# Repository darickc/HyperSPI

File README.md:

# HyperSPI
SPI bridge for AWA protocol to control a LED strip from HyperHDR.  
Diagnostic and performance data available at the serial port output [read more](#performancedebug-output).  
Raspberry Pi acts as a master, ESP8266/ESP32/ESP32-S2/rp2040(Raspberry Pi Pico) is in slave mode. 
  
| LED strip / Device             | rp2040 / Pico | ESP8266<br>(limited performance) |    ESP32 / ESP32-S2 mini    
|--------------------------------|:-------:|:-----------:|:-------:|
| SK6812 cold white              |   yes   |   yes   |     yes     |
| SK6812 neutral white           |   yes   |   yes   |     yes     |
| WS281x                         |   yes   |   yes   |     yes     |

# Why this project was created?

- SPI is very faster. HyperSPI works best at speed over 20Mb
- SPI doesn't have any data integration check. But AWA protocol does have one
- you don't need to have 2Mb capable serial port on your ESP board
- SPI transmission is much lighter than serial communication
- There is a hardware limitation for the Rpi current design...even if you connect your grabber using USB2.0 mode, working serial port driver (used by Adalight) results in quite a large drop in overall USB transfer. So we can replace Adalight with a pure SPI data transfer as an alternative
- I needed it and I was able to implemented it 😉

# Hardware connection  

If you are using an ESP board compatible with the Wemos board (ESP8266 Wemos D1/pro, ESP32 MH-ET Live, ESP32-S2 lolin mini), the SPI connection uses the same pinout location on the ESP board! The pin positions of the LED output may vary. Cables (including ground) should not exceed 15-20cm or it may be necessary to lower the SPI speed. 

The photos below use the same home-made adapter throughout, so you can see a repeating pattern and the cable colors should help you locate the correct pins. However, always consult the GPIO diagram for your boards to confirm that you have connected the cables correctly, because if you make a mistake and connect to the 5V GPIO line, it may damage both devices.  

As you can also notice, the pinout of the SPI0 interface is identical for the entire Raspberry Pi SBC family: 3, 4, 5, Zero 2W, etc.  

<table>  
  <tr>
    <td colspan="2"><p align="center">See how easy it is to connect Raspberry Pi Pico (rp2040) to Raspberry Pi 5 using SPI</p></td>    
  </tr>
  <tr>
    <td colspan="2"></td>
  </tr>
  <tr>
    <td></td>
    <td></td>
  </tr>
  <tr>
    <td colspan="2"><p align="center">or if you prefer ESP32/ESP32-S2/Esp8266</p></td>
  </tr>
  <tr>
    <td></td>
    <td></td>
  </tr>
  <tr>
    <td></td>
    <td></td>
  </tr> 
  <tr>
    <td colspan="2"><p align="center">multi-architecture support via FTDI (ex. FT232H)</p></td>
  </tr>
  <tr>
    <td colspan="2"></td>    
  </tr>  
</table>

# Example of supported boards

<p align="center">
<b>Adafruit RP2040 Scorpio and ItsyBitsy with built-in level shifter (recommended!)</b><br/>  

</p>

<p align="center">
<b>Esp8266 Wemos D1 mini (CH340) and Wemos D1 mini pro (CP2104)</b><br/>

</p>

<p align="center">
<b>ESP32 MH-ET Live and ESP32-S2 Lolin mini (CDC)</b><br/>

</p>

## Default pinout (can be changed for esp32, esp32-s2 and rp2040 Pico)
  
|    PINOUT   |  ESP8266  |   ESP32   | ESP32-S2 | Pico (rp2040) | Adafruit rp2040<br/>Scorpio / ItsyBitsy
|-------------|-----------|-----------|-----------|-----------|-----------|
| Clock (SCK) | GPIO 14   | GPIO 18   | GPIO 7    | GPIO 2    | GPIO 26 (A0) |
| Data (MOSI) | GPIO 13   | GPIO 23   | GPIO 11   | GPIO 4    | GPIO 28 (A2) |
| SPI Chip Select(e.g. CE0) | not used    | GPIO 5    | GPIO 12   | GPIO 5    | GPIO 29 (A3) |
| GROUND      | mandatory | mandatory | mandatory | mandatory | mandatory |
| LED output  | GPIO 2    | GPIO 2    | GPIO 2    | GPIO 14 | GPIO16 / GPIO14 |

> [!CAUTION]
> The ground connection between both GPIOs is as important as the other SPI data connections. The ground cable should be of a similar length as them and run directly next to them.

# Flashing the firmware

There are two versions of the firmware for ESP32 and ESP32-S2. The 'factory' (in the `recovery_firmware.zip` archive) and the 'base' one. Factory firmware should be flashed to offset 0x0, base firmware to offset 0x10000.

## Flashing ESP32-S2 Lolin mini

Requires using `esptool.py` to flash the firmware e.g.  
 - `esptool.py write_flash 0x10000 hyperspi_esp32_s2_mini_SK6812_RGBW_COLD.bin` or
 - `esptool.py write_flash 0x0 hyperspi_esp32_s2_mini_SK6812_RGBW_COLD.factory.bin`

Troubleshooting: ESP32-S2 Lolin mini recovery procedure if the board is not detected or is malfunctioning.  
1. Put the board into dfu mode using board buttons: press `Rst` + `0` buttons, then release `Rst`, next release `0`  
Do not reset or disconnect the board until the end of the recovery procedure.
2. Execute `esptool.py erase_flash`  
3. Flash 'factory' version of the firmware e.g.  
`esptool.py write_flash 0x0 hyperspi_esp32_s2_mini_SK6812_RGBW_COLD.factory.bin`  
4. **`esptool.py` is not able to automatically reset esp32-s2 when in dfu mode. Reconnect or hard reset it manually.** The board should be detected as a COM port in the system.

## Flashing generic Esp8266/ESP32

Recommend to use [esphome-flasher](https://github.com/esphome/esphome-flasher/releases)  
Or use `esptool.py` e.g.  
 - `esptool.py write_flash 0x10000 hyperspi_esp32_SK6812_RGBW_COLD.bin` or
 - `esptool.py write_flash 0x0 hyperspi_esp32_SK6812_RGBW_COLD.factory.bin`

For **RGBW LED strip** like RGBW SK6812 NEUTRAL white choose: *hyperspi_..._SK6812_RGBW_NEUTRAL.bin*  
For **RGBW LED strip** like RGBW SK6812 COLD white choose: *hyperspi_..._SK6812_RGBW_COLD.bin*  
For **RGB LED strip** like WS8212b or RGB SK6812 variant choose: *hyperspi_..._WS281x_RGB.bin*  

## Flashing Pico boards

It's very easy and you don't need any special flasher.  

Use firmware from the `hyperspi_pico_rp2040.zip` archive. Adafruit boards have their own custom firmware package inside the archive: `Adafruit_ItsyBitsy_RP2040.zip` and `Adafruit_Feather_RP2040_Scorpio.zip`

Put your Pico board into DFU mode:  
* If your Pico board has only one button (`boot`) then press & hold it and connect the board to the USB port. Then you can release the button.
* If your Pico board has two buttons, connect it to the USB port. Then press & hold `boot` and `reset` buttons, then release `reset` and next release `boot` button.  

In the system file explorer you should find new drive (e.g. called `RPI-RP2` drive) exposed by the Pico board. Drag & drop (or copy) the selected firmware to this drive. 
The Pico will reset automaticly after the upload and after few seconds it will be ready to use.
  
# Software configuration (HyperHDR v17 and above)

**In HyperHDR `Image Processing→Smoothing→Update frequency` you should do not exceed the maximum capacity of the device. Read more here: [testing performance](https://github.com/awawa-dev/HyperSPI#performance-output)**

Select `esp8266` protocol for ESP proprietary SPI protocol, `esp32` for ESP32 boards, `rp2040 (Pico)` for Pico boards or `standard` for other devices.    
Make sure you set "Refresh time" to zero, "Baudrate" should be set to high but realistic value like ```25 000 000```.  
Enabling "White channel calibration" is optional, if you want to fine tune the white channel balance of your sk6812 RGBW LED strip.

# Benchmark results

## ESP32 & ESP32-S2 parallel multi-segment mode

| sk6812 LED strip / Device                                                                      | ESP32 MH-ET LIVE mini<br/>HyperSPI v9 |  ESP32-S2 Lolin mini<br/>HyperSPI v9 |
|-----------------------------------------------------------------------------------------|-----------------------|----------------------|
| 300 RGBW LEDs<br>Refresh rate/continues output=100Hz<br>SECOND_SEGMENT_START_INDEX=150 |          100          |          100         |
| 600 RGBW LEDs<br>Refresh rate/continues output=83Hz<br>SECOND_SEGMENT_START_INDEX=300  |           83          |           83         |
| 900 RGBW LEDs<br>Refresh rate/continues output=55Hz <br>SECOND_SEGMENT_START_INDEX=450 |         54-55         |           55         |

## SP8266 / ESP32

| sk6812 LED strip / Device                             | ESP32 MH ET Live<br/>HyperSPI v9 | ESP32-S2 Lolin mini<br/>HyperSPI v9 | ESP8266 Wemos D1 Pro<br/>HyperSPI v9 |
|------------------------------------------------|-----------------|--------------------|---------------------|
| 300 RGBW LEDs<br>continues output=83/70Hz  |        83       |          83        |          70         |
| 600 RGBW LEDs<br>continues output=43/33Hz  |      42-43      |          42        |          33         |
| 900 RGBW LEDs<br>continues output=28/22Hz  |       28        |          28        |          22         |

# Compiling

## ESP8266 / ESP32

Currently we use PlatformIO to compile the project. Install [Visual Studio Code](https://code.visualstudio.com/) and add [PlatformIO plugin](https://platformio.org/).
This environment will take care of everything and compile the firmware for you. Low-level LED strip support is provided by my highly optimizated (pre-fill I2S DMA modes, turbo I2S parallel mode for up to 2 segments etc) version of Neopixelbus library: [link](https://github.com/awawa-dev/NeoPixelBus).

## Pico rp2040

Use Pico SDK and Visual Code to open ```rp2040``` folder. Edit ```rp2040\CMakeLists.txt``` configuration file if you need to apply changes.

## Github Action

But there is also an alternative and an easier way. Just fork the project and enable its Github Action. Use the online editor to make changes:
- esp8266/ESP32 boards: to the ```platformio.ini``` file
- rp2040 Pico boards: to the ```rp2040\CMakeLists.txt``` file

for example change default pin-outs or enable multi-segments support, and save it. Github Action will compile new firmware automatically in the Artifacts archive. It has never been so easy! **Just remember to follow the steps in the correct order otherwise the Github Action may not be triggered the first time after saving the changes.**

Tutorial: https://github.com/awawa-dev/HyperSPI/wiki

# Multi-Segment Wiring (ESP32, ESP32-S2 and Pico rp2040 boards only)

## ESP32

Using parallel multi-segment allows you to double your Neopixel (e.g. sk6812 RGBW) LED strip refresh rate by dividing it into two smaller equal parts. Both smaller segments are perfectly in sync so you don't need to worry about it. Proposed example of building a multisegment:
- Divide a long or dense strip of LEDs into 2 smaller equal parts. So `SECOND_SEGMENT_START_INDEX` in the HyperSPI firmware is the total number of LEDs divided by 2.
- Build your first segment traditional way e.g. clockwise, so it starts somewhere in middle of the bottom of frame/TV and ends in the middle of the top of frame/TV
- Start the second segment in the opposite direction to the first one e.g. counterclockwise (`SECOND_SEGMENT_REVERSED` option in the HyperSPI firmware configuration must be enabled). So it starts somewhere in the middle of the bottom of the frame/TV and ends in the middle of the top of the TV/frame. Both segments could be connected if possible at the top but only 5v and ground ( NOT the data line).
- The data line starts for both segments somewhere in the middle of the bottom of the TV/frame (where each of the LED strips starts)
- Configuration in HyperHDR does not change! It's should be configured as one, single continues segment. All is done in HyperSPI firmware transparently and does not affect LED strip configuration in HyperHDR.

You also must configure data pin in the `platformio.ini`. Review the comments at the top of the file:
* `SECOND_SEGMENT_DATA_PIN` - These is data pin for your second strip

You add these to your board's config. Be sure to put `-D` in front of each setting. 

Examples of final build_flags for 288 LEDs divided into 2 equal segments in the `platformio.ini`:
```
[env:SK6812_RGBW_COLD]
build_flags = -DNEOPIXEL_RGBW -DCOLD_WHITE -DDATA_PIN=2 ${env.build_flags} -DSECOND_SEGMENT_START_INDEX=144 -DSECOND_SEGMENT_DATA_PIN=4 -DSECOND_SEGMENT_REVERSED
...
[env:WS281x_RGB]
build_flags = -DNEOPIXEL_RGB -DDATA_PIN=2 ${env.build_flags} -DSECOND_SEGMENT_START_INDEX=144 -DSECOND_SEGMENT_DATA_PIN=4 -DSECOND_SEGMENT_REVERSED
...
```
Implementation example:
- The diagram of the board for WS2812b/SK6812 including ESP32 and the SN74AHCT125N 74AHCT125 [level shifter](https://github.com/awawa-dev/HyperHDR/wiki/Level-Shifter).

## Pico rp2040

Edit ```rp2040\CMakeLists.txt``` file and recompile the project.

# Automatic LED Power Control (ESP32)

HyperSPI can optionally drive a relay (or a MOSFET power switch) that disconnects the **positive 5V supply of the LED strip** when there is nothing to display, similar to the relay feature of WLED and HyperSerialESP32. The feature is compiled in only when `LED_POWER_PIN` is defined. Without it the firmware behaves exactly as before.

Tested target: ESP32-WROOM-32 (`esp32dev`). The code only uses `pinMode`/`digitalWrite`/`millis`, but other boards have not been verified.

## How to enable it

Use one of the ready-made environments. Both use data on GPIO2 and an active-high power switch on GPIO16, matching the P-MOSFET board in [`hardware/hyperspi-led-controller`](hardware/hyperspi-led-controller):

| LED strip | Environment | Firmware |
|---|---|---|
| SK6812 RGBW cold white | `SK6812_RGBW_COLD_LED_POWER` | `hyperspi_esp32_SK6812_RGBW_COLD_LED_POWER.bin` |
| WS281x RGB (WS2812B etc.) | `WS281x_RGB_LED_POWER` | `hyperspi_esp32_WS281x_RGB_LED_POWER.bin` |

```
pio run -e SK6812_RGBW_COLD_LED_POWER
```
You can also append the flags to the `build_flags` of any ESP32 environment in `platformio.ini`:
```ini
; active-low relay module (IN = LOW switches the LED power on)
build_flags = -DNEOPIXEL_RGB -DDATA_PIN=2 ${env.build_flags} -DLED_POWER_PIN=16 -DLED_POWER_INVERT

; active-high relay module or MOSFET board (IN = HIGH switches the LED power on)
build_flags = -DNEOPIXEL_RGB -DDATA_PIN=2 ${env.build_flags} -DLED_POWER_PIN=16
```

| Flag | Default | Description |
|---|---|---|
| `LED_POWER_PIN` | not defined (feature disabled) | GPIO connected to the relay control input |
| `LED_POWER_INVERT` | not defined (active-high) | Define it for active-low relay modules |
| `LED_POWER_OFF_DELAY` | `5000` | How long (ms) the LEDs must stay completely black before the power is switched off |
| `LED_POWER_ON_DELAY` | `200` | Time (ms) the LED supply gets to stabilize before the first frame is sent to the strip |
| `LED_POWER_IDLE_TIMEOUT` | `5000` | Time (ms) without any valid frame before the power is switched off. `0` disables it |
| `LED_POWER_DEBUG` | not defined | Prints `[LED POWER] ...` messages to the serial port (115200) on state changes only |

## Recommended GPIO

- **GPIO16** (default in the example). It is not a strapping pin and is not used by HyperSPI. Note: on WROVER modules GPIO16/17 are used by the PSRAM, so pick another pin there.
- Alternatives: GPIO17, 25, 26, 27, 32, 33.
- Avoid the strapping pins GPIO0, 2, 5, 12 and 15. Avoid the flash pins GPIO6–11, and the input-only pins GPIO34–39.
- HyperSPI already uses: SCK GPIO18, MISO GPIO19, MOSI GPIO23, CS GPIO5, LED data GPIO2 (and the second segment data pin if configured).

## Wiring

```
 5V PSU (+) ──── relay COM ──── relay NO ──── LED strip +5V
 5V PSU (−) ──────────────────────────────── LED strip GND ──── ESP32 GND ──── Raspberry Pi GND
 ESP32 GPIO16 ──────────── relay IN
 ESP32 GPIO2 ── level shifter (e.g. 74AHCT125) ── 330 Ω ── LED strip DIN
 ESP32 powered independently (USB or its own 5V supply that is NOT switched by the relay)
```

- The relay switches **only the positive 5V supply of the LED strip**. Never switch the ground: an LED strip with a floating ground can find a ground path through the data line and the ESP32.
- The ESP32 must stay powered while the LED power is off, otherwise it cannot switch it on again.
- The ESP32, the LED strip, the power supply and the Raspberry Pi must share a common ground.
- The relay or power switch must be rated for the **maximum DC current of the LED strip and its inrush current** when it is switched on, which can be a lot higher than the steady current. Mechanical relays are often rated for AC. Check the DC rating, or use a suitably rated logic-level MOSFET/high-side switch for higher currents.
- **Back-powering:** an unpowered addressable LED can be partly powered through its data input. HyperSPI does not render anything while the LED power is off, so the data line stays idle (low). A 3.3V→5V level shifter such as the 74AHCT125 / SN74AHCT1G125 powered from the unswitched 5V (the ESP32 side, not the relay output), plus a 220–470 Ω series resistor close to the strip, isolates the ESP32 GPIO and limits any current. A level shifter is recommended anyway for reliable 5V LED data.
- **Active-low modules:** many common opto-isolated relay boards switch on when IN is pulled LOW. If the module is powered from 5V, a 3.3V HIGH level from the ESP32 may not fully release the relay. Prefer a module that is specified for 3.3V logic or as a "high level trigger" type, power its input side from 3.3V if the board allows it (separate JD-VCC jumper), or use a transistor/MOSFET stage.

### Boot state

The firmware sets the relay pin to its inactive level as the first step of `setup()`, before the serial port, the LED driver and SPI are started. The level is written before the pin becomes an output, so there is no glitch. However, **software cannot control the pin during the ESP32 hardware reset and bootloader period** (a few hundred ms after power-up, reset or flashing). During that time GPIO16 is a high-impedance input. To keep the relay off during that time, add an external resistor:
- active-high module: 10 kΩ pull-down from the GPIO to GND
- active-low module: 10 kΩ pull-up from the GPIO to the logic level of the relay input

## Expected behavior

| Situation | Relay |
|---|---|
| ESP32 boots | OFF |
| Invalid/damaged frame (CRC or Fletcher checksum fails) | No change |
| Valid frame that is completely black, relay OFF | Stays OFF (the frame is not sent to the strip) |
| First valid non-black frame | ON. The frame is held for `LED_POWER_ON_DELAY` and then rendered, even if HyperHDR sends nothing more |
| Normal frames | Stays ON. The GPIO is written only when the state changes |
| Black scene shorter than `LED_POWER_OFF_DELAY` | Stays ON (black frames are rendered normally) |
| Black for `LED_POWER_OFF_DELAY` | OFF (measured from the first black frame, so it also works when HyperHDR sends black and then goes silent) |
| No valid frame for `LED_POWER_IDLE_TIMEOUT` | OFF (only if the timeout is not `0`) |
| Non-black frame while OFF | ON again, after the stabilization delay |

With multiple segments, the relay is treated as one shared power supply. The frame is black only if all LEDs of all segments are black.

All timers are non-blocking (`millis()` based and safe across its rollover), so SPI reception and LED rendering are not delayed.

## HyperHDR behavior and settings

- When you disable the LED device in HyperHDR (or stop it), HyperHDR sends 2 black frames and closes the SPI device. The relay switches off `LED_POWER_OFF_DELAY` later.
- The Awa protocol has no power on/off command. The relay is controlled only by the frame content and by timing.
- With `Image Processing→Smoothing` enabled (the HyperHDR default), a static image is still re-sent about once per second, which keeps the default 5 s `LED_POWER_IDLE_TIMEOUT` from triggering.
- **Limitation:** a static image that is not re-sent and a stopped or crashed host look identical over SPI. If you disable Smoothing or see the LEDs switch off while showing a static color, either enable `Smoothing→Continuous output` (consider a lower update frequency), or build with `-DLED_POWER_IDLE_TIMEOUT=0`. With `0`, the relay switches off only after black frames, so a crashed host leaves the LEDs on with the last image.
- Keep "Refresh time" at 0 as recommended above. It is not needed for this feature.

## Troubleshooting

- **Relay never switches on**: check the polarity (`LED_POWER_INVERT`), and check that the module accepts a 3.3V control signal. Enable `LED_POWER_DEBUG` and look for `[LED POWER] Relay ON` in the serial output. Black content never switches the relay on.
- **Relay clicks on at power-up or reset**: add the pull-up/pull-down resistor described above.
- **First frame is missing or flickers after power-on**: increase `LED_POWER_ON_DELAY` (e.g. 500) for power supplies that are slow to stabilize.
- **LEDs switch off during a static color**: see the idle timeout limitation above.
- **LEDs switch off too quickly in dark movie scenes**: increase `LED_POWER_OFF_DELAY` (e.g. 30000).
- **ESP32 resets when the relay switches**: the inrush current or relay coil is pulling the supply down. Power the ESP32 separately, add bulk capacitance (e.g. 1000 µF) at the strip input, and keep the relay coil supply away from the ESP32 3.3V regulator.

# Performance/debug output

**The output is only available when HyperHDR is not using the device at the moment, so it should be disabled in the app for a while.** Stores the last result when HyperHDR was running in the current session. You can read it from the serial port at a speed of 115200.

On Linux you can `screen` command.  
First install it: `sudo apt install screen`. Adjust USB port if necessary and connect to the serial port:  
`screen /dev/ttyACM0 115200`  
If you want to exit screen press `Ctrl-a` then `k` and confirm exit.

You can also use `Putty` on Windows

For testing maximum performance in HyperHDR enable `Image Processing→Smoothing→Continuous output`, high `Update frequency` in the same tab and set any color in the `Remote control` tab as an active effect. After testing you need to disable `Continuous output`and set `Update frequency` according to your results.

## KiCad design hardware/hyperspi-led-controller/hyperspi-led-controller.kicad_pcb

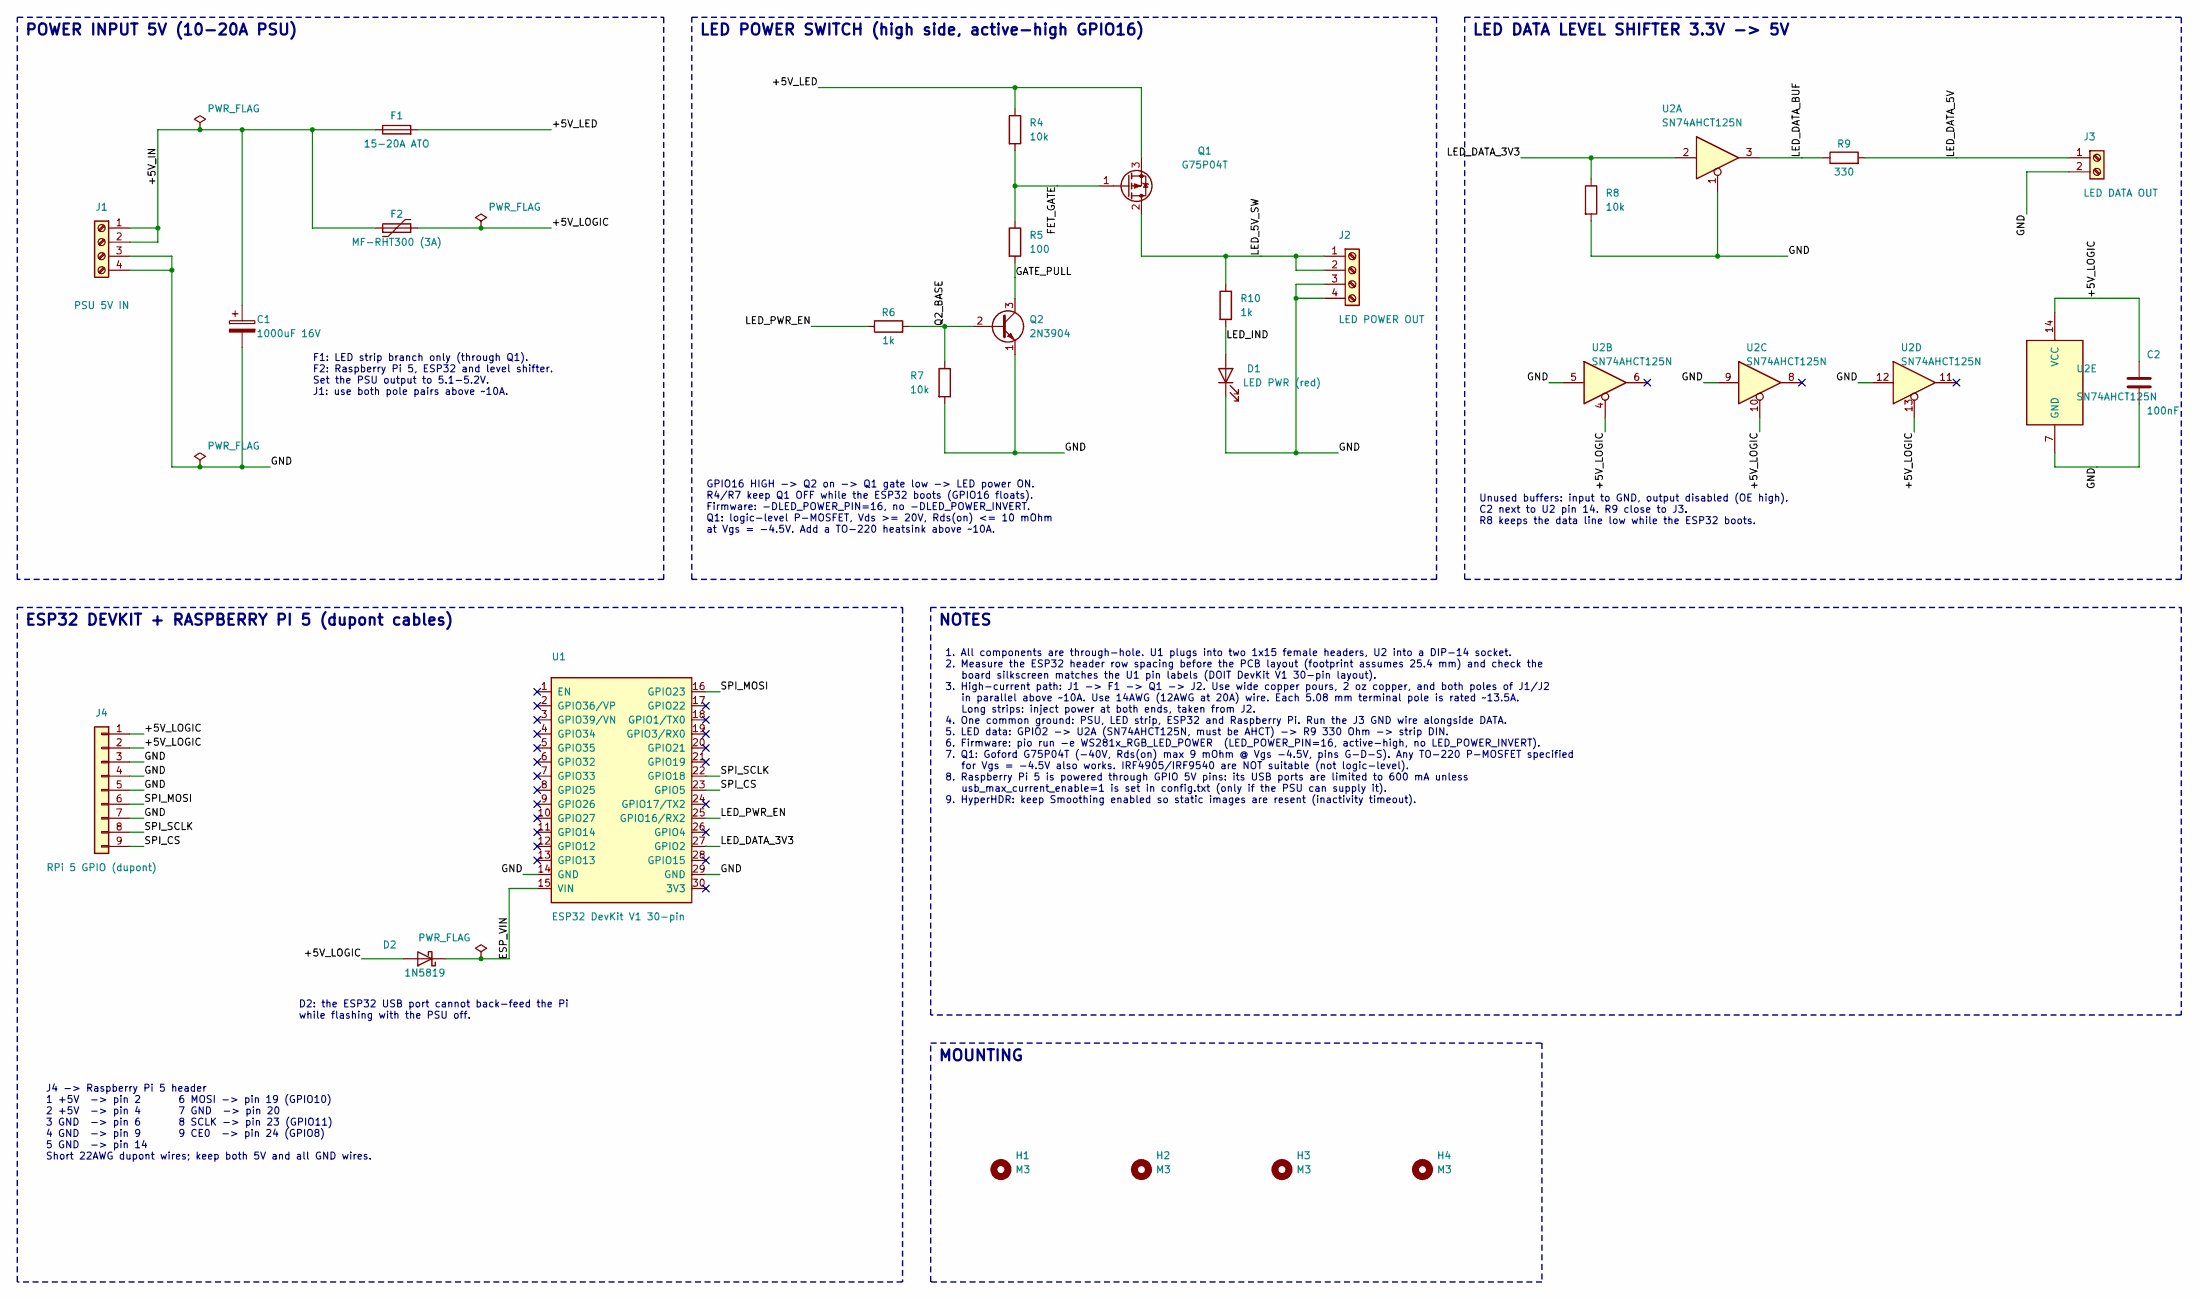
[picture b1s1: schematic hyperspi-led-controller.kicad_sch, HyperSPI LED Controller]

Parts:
C1: 1000uF 16V; CP_Radial_D10.0mm_P5.00mm
C2: 100nF; C_Disc_D5.0mm_W2.5mm_P5.00mm
D1: LED PWR (red); LED_D3.0mm
D2: 1N5819; D_DO-41_SOD81_P10.16mm_Horizontal
F1: 15-20A ATO; FuseHolder_Blade_ATO_Littelfuse_FLR_178.6165
F2: MF-RHT300 (3A); Fuse_Bourns_MF-RHT300
H1, H2, H3, H4: M3; MountingHole_3.2mm_M3
J1: PSU 5V IN; TerminalBlock_Phoenix_MKDS-1,5-4-5.08_1x04_P5.08mm_Horizont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
J2: LED POWER OUT; TerminalBlock_Phoenix_MKDS-1,5-4-5.08_1x04_P5.08mm_Horizont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
J3: LED DATA OUT; TerminalBlock_Phoenix_MKDS-1,5-2-5.08_1x02_P5.08mm_Horizont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
J4: RPi 5 GPIO (dupont); PinHeader_1x09_P2.54mm_Vertical
Q1: G75P04T; TO-220-3_Vertical
Q2: 2N3904; TO-92_Inline
R4, R7, R8: 10k; R_Axial_DIN0207_L6.3mm_D2.5mm_P10.16mm_Horizontal
R5: 100; R_Axial_DIN0207_L6.3mm_D2.5mm_P10.16mm_Horizontal
R6, R10: 1k; R_Axial_DIN0207_L6.3mm_D2.5mm_P10.16mm_Horizontal
R9: 330; R_Axial_DIN0207_L6.3mm_D2.5mm_P10.16mm_Horizontal
U1: ESP32 DevKit V1 30-pin; ESP32_DevKit_V1_30pin_Socket
U2: SN74AHCT125N; DIP-14_W7.62mm_Socket

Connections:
/+5V_IN: C1.1, F1.1, F2.1, J1.1, J1.2
/+5V_LED: F1.2, Q1.3 (S), R4.1
/+5V_LOGIC: C2.1, D2.2 (A), F2.2, J4.1, J4.2, U2.4, U2.10, U2.13, U2.14 (VCC)
/ESP_VIN: D2.1 (K), U1.15 (VIN)
/FET_GATE: Q1.1 (G), R4.2, R5.1
/GATE_PULL: Q2.3 (C), R5.2
/GND: C1.2, C2.2, D1.1 (K), J1.3, J1.4, J2.3, J2.4, J3.2, J4.3, J4.4, J4.5, J4.7, Q2.1 (E), R7.2, R8.2, U1.14 (GND), U1.29 (GND), U2.1, U2.5, U2.7 (GND), U2.9, U2.12
/LED_5V_SW: J2.1, J2.2, Q1.2 (D), R10.1
/LED_DATA_3V3: R8.1, U1.27 (GPIO2), U2.2
/LED_DATA_5V: J3.1, R9.2
/LED_DATA_BUF: R9.1, U2.3
/LED_IND: D1.2 (A), R10.2
/LED_PWR_EN: R6.1, U1.25 (GPIO16/RX2)
/Q2_BASE: Q2.2 (B), R6.2, R7.1
/SPI_CS: J4.9, U1.23 (GPIO5)
/SPI_MOSI: J4.6, U1.16 (GPIO23)
/SPI_SCLK: J4.8, U1.22 (GPIO18)

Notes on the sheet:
POWER INPUT 5V (10-20A PSU)
F1: LED strip branch only (through Q1). F2: Raspberry Pi 5, ESP32 and level shifter. Set the PSU output to 5.1-5.2V. J1: use both pole pairs above ~10A.
LED POWER SWITCH (high side, active-high GPIO16)
GPIO16 HIGH -> Q2 on -> Q1 gate low -> LED power ON. R4/R7 keep Q1 OFF while the ESP32 boots (GPIO16 floats). Firmware: -DLED_POWER_PIN=16, no -DLED_POWER_INVERT. Q1: logic-level P-MOSFET, Vds >= 20V, Rds(on) <= 10 mOhm at Vgs = -4.5V. Add a TO-220 heatsink above ~10A.
LED DATA LEVEL SHIFTER 3.3V -> 5V
Unused buffers: input to GND, output disabled (OE high). C2 next to U2 pin 14. R9 close to J3. R8 keeps the data line low while the ESP32 boots.
ESP32 DEVKIT + RASPBERRY PI 5 (dupont cables)
D2: the ESP32 USB port cannot back-feed the Pi while flashing with the PSU off.
J4 -> Raspberry Pi 5 header 1 +5V -> pin 2 6 MOSI -> pin 19 (GPIO10) 2 +5V -> pin 4 7 GND -> pin 20 3 GND -> pin 6 8 SCLK -> pin 23 (GPIO11) 4 GND -> pin 9 9 CE0 -> pin 24 (GPIO8) 5 GND -> pin 14 Short 22AWG dupont wires; keep both 5V and all GND wires.
MOUNTING
NOTES
1. All components are through-hole. U1 plugs into two 1x15 female headers, U2 into a DIP-14 socket. 2. Measure the ESP32 header row spacing before the PCB layout (footprint assumes 25.4 mm) and check the board silkscreen matches the U1 pin labels (DOIT DevKit V1 30-pin layout). 3. High-current path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

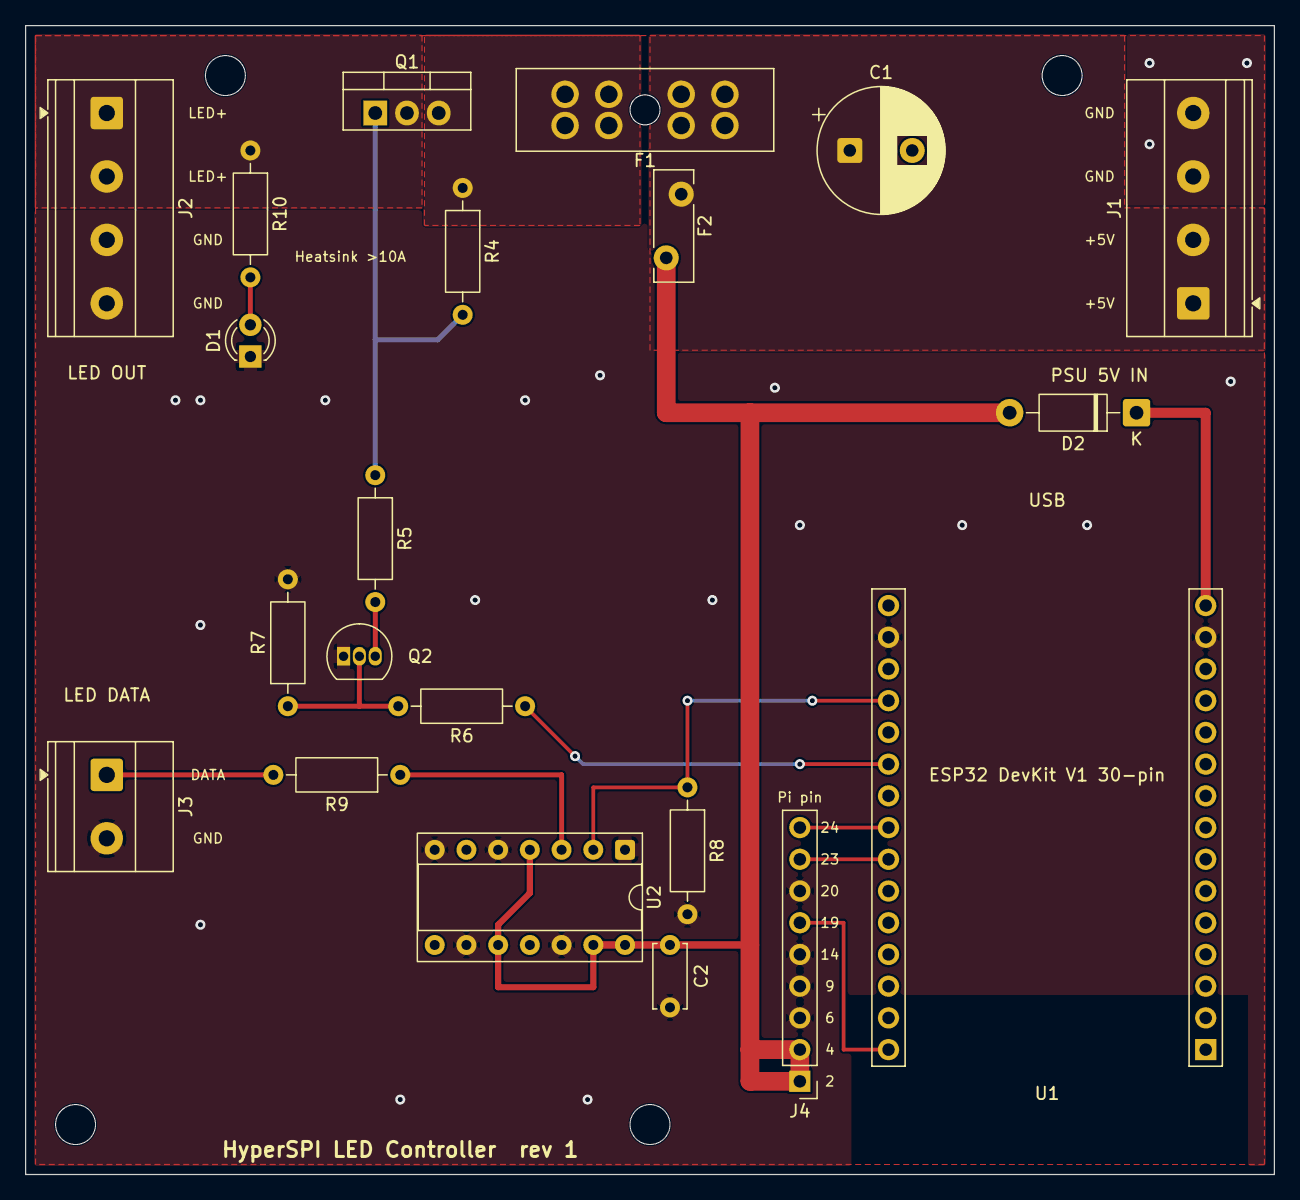
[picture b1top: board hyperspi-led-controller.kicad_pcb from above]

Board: 2 copper layers, 100.0 x 92.0 mm, 25 parts (0 on the bottom side), 17 nets.

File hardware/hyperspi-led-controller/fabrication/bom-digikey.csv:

Refs,Qty,Value,Manufacturer,MPN,DigiKey PN,Unit price (qty 1),DigiKey stock 2026-10-21,Notes
"J1,J2",2,5.08mm 4-pos screw terminal,Phoenix Contact,1715747,277-1265-ND,$2.28,1348,MKDS 1.5/4-5.08; 15 A per pole
J3,1,5.08mm 2-pos screw terminal,Same Sky,TB007-508-02BE,102-6203-ND,$0.53,14260,Phoenix 1715721 (277-1263-ND; $1.16) matches J1/J2 but is out of stock (backorder; 6 wk lead time)
F1,1,ATO blade fuse holder (PCB),Littelfuse,178.6165.0002,WK6265-ND,$5.72,14511,Matches footprint FuseHolder_Blade_ATO_Littelfuse_FLR_178.6165
F1 fuse,1,ATO fuse 15 A,Littelfuse,0287015.PXCN,F4200-ND,$0.44,45707,Size to the LED strip. 20 A = 0287020.PXCN (F4201-ND; $0.44; 59509). The 0257 series is obsolete
F2,1,PTC 3 A hold 16 V,Bourns,MF-RHT300-0,118-MF-RHT300-0-ND,$0.99,1982,
J4,1,1x9 male header 2.54mm,Sullins,PRPC009SAAN-RC,35-PRPC009SAAN-RC-ND,$0.18,1789,
U1 sockets,2,1x15 female header 2.54mm,Sullins,PPTC151LFBN-RC,S7013-ND,$0.92,17438,For the ESP32 DevKit (board itself from Amazon)
U2 socket,1,DIP-14 socket,On Shore Technology,ED14DT,ED3045-5-ND,$0.52,10554,
U2,1,SN74AHCT125N,Texas Instruments,SN74AHCT125N,296-4655-5-ND,$1.00,1846,Already owned (Amazon) - skip if you have it
Q1,1,P-MOSFET 40 V logic-level TO-220,Goford Semiconductor,G75P04T,3141-G75P04T-ND,$2.09,3,Replaces obsolete IPP80P03P4L-04. Datasheet: Rds(on) max 9 mOhm @ Vgs -4.5 V (6.8 typ); pinout G-D-S (matches footprint). Only 3 in stock
Q1 heatsink,1,TO-220 bolt-on heatsink 24.4 C/W,Boyd,577202B00000G,HS107-ND,$1.72,53891,Optional; recommended above ~10 A (about 15 A comfortable with this one). Needs M3 screw + thermal pad; tab is the drain (LED_5V_SW)
Q2,1,2N3904 NPN TO-92,onsemi,2N3904BU,2N3904FS-ND,$0.29,305183,
D2,1,1N5819 Schottky DO-41,Taiwan Semiconductor,1N5819,1801-1N5819CT-ND,$0.32,9767,
D1,1,LED red 3mm diffused,Kingbright,WP710A10ID,754-1606-ND,$0.24,156303,
C1,1,1000uF 16V radial 10x20mm 5mm pitch,Nichicon,UHE1C102MPD,493-1526-ND,$0.97,13725,Panasonic EEU-FR1C102 is out of stock (37 wk lead time)
C2,1,100nF 50V X7R radial 5.08mm,KEMET,C322C104K5R5TA,399-4329-ND,$1.49,25199,
"R4,R7,R8",3,10k 1/4W 5% carbon film,Stackpole,CF14JT10K0,CF14JT10K0CT-ND,$0.10,564157,
R5,1,100 1/4W 5% carbon film,Stackpole,CF14JT100R,CF14JT100RCT-ND,$0.10,291582,
"R6,R10",2,1k 1/4W 5% carbon film,Stackpole,CF14JT1K00,CF14JT1K00CT-ND,$0.10,593503,
R9,1,330 1/4W 5% carbon film,Stackpole,CF14JT330R,CF14JT330RCT-ND,$0.10,282801,
